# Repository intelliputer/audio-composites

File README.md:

## audio-composites

Since just seeing isn't believing.

## Intellivision mono audio line driver

This repository now contains a standalone audio-output prototype for the NTSC
Intellivision I, Intellivision II, and Sears 497.75022. It taps the console's
pre-RF mono audio, buffers it with a two-transistor gain/line-driver stage,
and returns a buffered mono line to the video-composite board's audio-output
connection.
It does not create stereo or alter the console's sound generation.

The project is intentionally separate from the composite-video board so audio
level, hum, loading, and video interaction can be tested independently. It is
intended to mount as a daughterboard beside that board, using four short wires:
raw audio, buffered audio return, +5 V, and ground. The video board's original
straight-through audio capacitor is bypassed.

### Current status: routed prototype, not yet fabrication-ready

[`project/intv-audio-line-driver.kicad_pcb`](project/intv-audio-line-driver.kicad_pcb)
is a fully routed KiCad Rev. A board. Its routing report has zero DRC
violations and zero unconnected pads. It remains explicitly marked **DO NOT
FAB** because the inherited KiCad schematic has not yet been rewritten to
match the new audio netlist, and the circuit still requires bench validation.

The circuit, component values, and first-article checks are defined in
[`project/REV-A-CIRCUIT.md`](project/REV-A-CIRCUIT.md). The placement can be
recreated through KiCad Flatpak with
[`project/tools/generate_rev_a_pcb.py`](project/tools/generate_rev_a_pcb.py).

The next compact, hand-assembled revision is specified in
[`project/REV-B-KA358-PDIP.md`](project/REV-B-KA358-PDIP.md). It replaces the
discrete stage with a KA358-compatible PDIP-8 dual op amp. Its enlarged
two-layer through-hole routing handoff is in
[`project/intv-audio-line-driver-rev-b.kicad_pcb`](project/intv-audio-line-driver-rev-b.kicad_pcb);
it is deliberately marked **DO NOT FAB** pending a reviewed schematic and
manual routing/DRC cleanup.

Before any fabrication release:

1. Redraw the KiCad schematic from the Rev. A circuit contract.
2. Update the PCB from that schematic and rerun ERC/DRC.
3. Test a first article under a line-level load.

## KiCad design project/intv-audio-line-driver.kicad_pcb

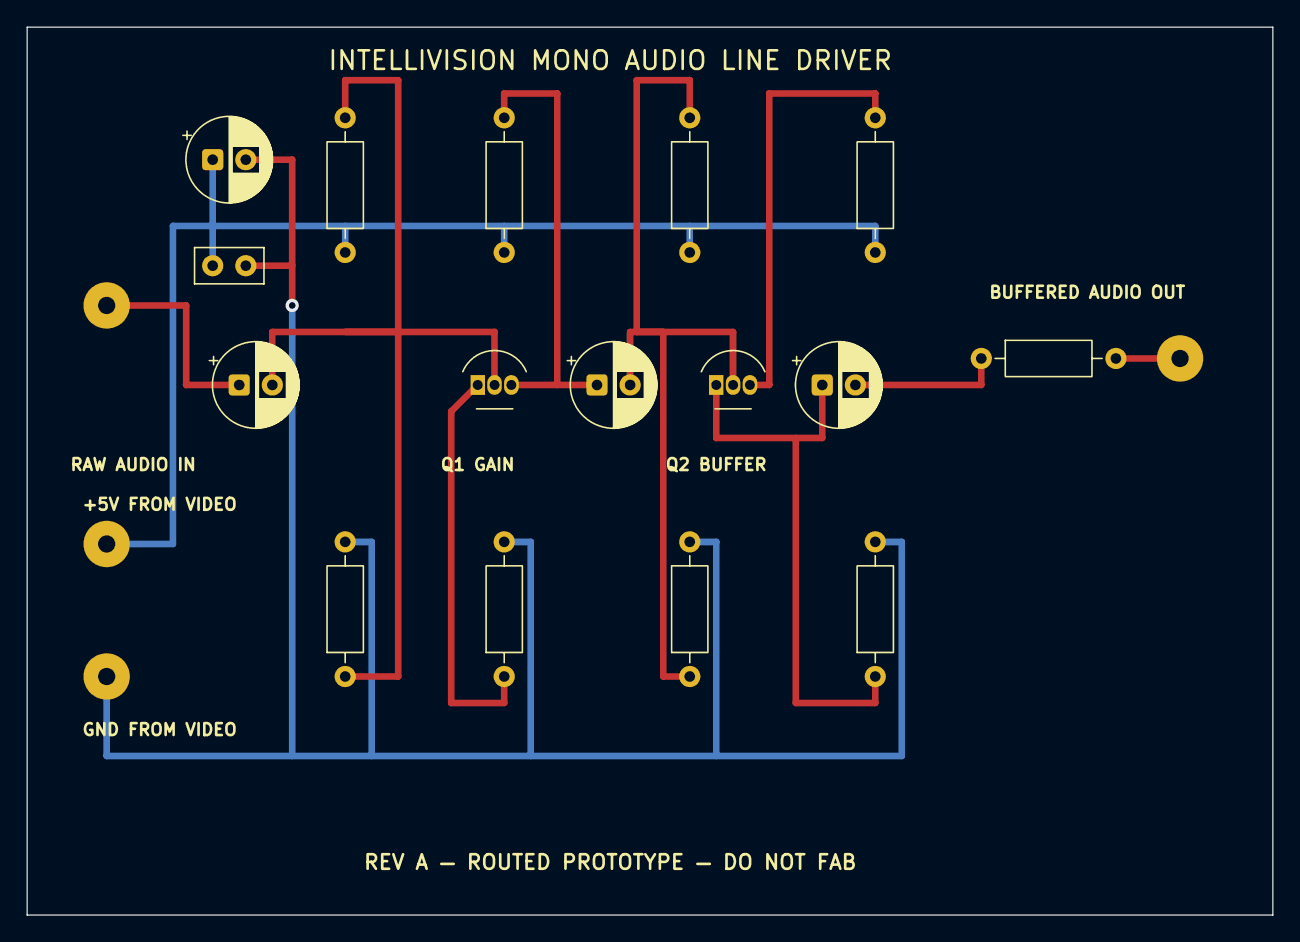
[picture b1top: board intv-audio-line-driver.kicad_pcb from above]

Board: 2 copper layers, 94.0 x 67.0 mm, 20 parts (0 on the bottom side), 11 nets.

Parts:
C1, C2: 10u; CP_Radial_D6.3mm_P2.50mm
C3, C4: 100u; CP_Radial_D6.3mm_P2.50mm
C5: 100n; C_Disc_D5.0mm_W2.5mm_P2.50mm
J1: RAW AUD IN; WirePad_1x01_D3.5mm_Drill1.3mm
J2: BUF AUD OUT; WirePad_1x01_D3.5mm_Drill1.3mm
J3: +5V FROM VID; WirePad_1x01_D3.5mm_Drill1.3mm
J4: GND FROM VID; WirePad_1x01_D3.5mm_Drill1.3mm
Q1, Q2: 2N3904; TO-92_Inline_OAR175
R1: 68k; R_Axial_DIN0207_L6.3mm_D2.5mm_P10.16mm_Horizontal
R2: 22k; R_Axial_DIN0207_L6.3mm_D2.5mm_P10.16mm_Horizontal
R3: 4.7k; R_Axial_DIN0207_L6.3mm_D2.5mm_P10.16mm_Horizontal
R4, R8, R9: 1k; R_Axial_DIN0207_L6.3mm_D2.5mm_P10.16mm_Horizontal
R5, R6: 33k; R_Axial_DIN0207_L6.3mm_D2.5mm_P10.16mm_Horizontal
R7: 0R; R_Axial_DIN0207_L6.3mm_D2.5mm_P10.16mm_Horizontal

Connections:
+5V: C4.1, C5.1, J3.1, R1.1, R3.1, R5.1, R7.1
AUDIO_BUS: C3.2, R9.1
AUD_IN: C1.1, J1.1
AUD_OUT: J2.1, R9.2
GND: C4.2, C5.2, J4.1, R2.2, R4.2, R6.2, R8.2
Q1_BASE: C1.2, Q1.2, R1.2, R2.1
Q1_COL: C2.1, Q1.3, R3.2
Q1_EM: Q1.1, R4.1
Q2_BASE: C2.2, Q2.2, R5.2, R6.1
Q2_COL: Q2.3, R7.2
Q2_EM: C3.1, Q2.1, R8.1

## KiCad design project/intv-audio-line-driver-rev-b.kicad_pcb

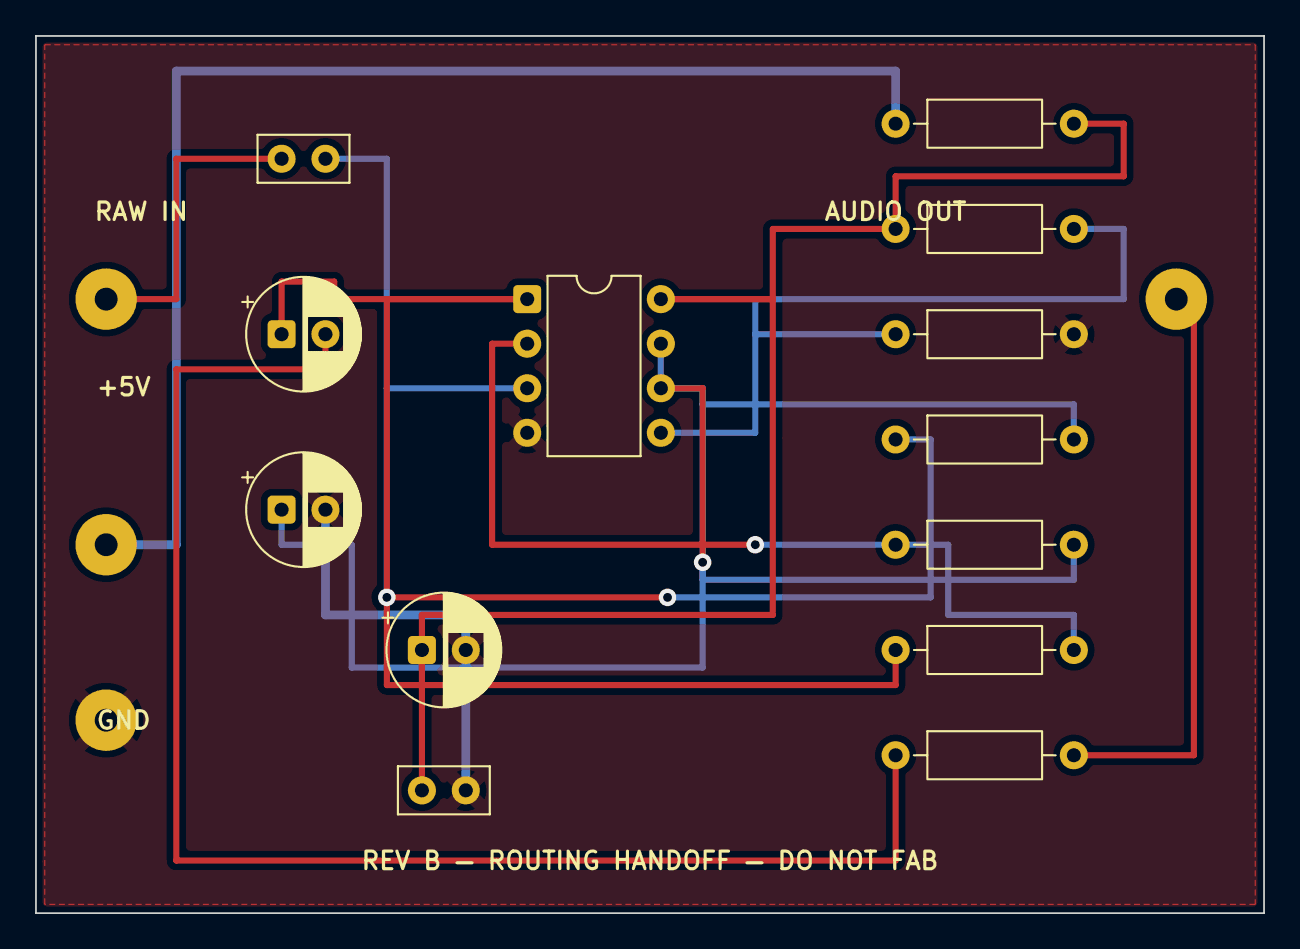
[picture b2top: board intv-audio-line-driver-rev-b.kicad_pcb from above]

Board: 2 copper layers, 70.0 x 50.0 mm, 17 parts (0 on the bottom side), 11 nets.

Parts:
C1: 1u; C_Disc_D5.0mm_W2.5mm_P2.50mm
C2, C3: 47u; CP_Radial_D6.3mm_P2.50mm
C4: 10u; CP_Radial_D6.3mm_P2.50mm
C5: 100n; C_Disc_D5.0mm_W2.5mm_P2.50mm
J1: RAW AUDIO IN; WirePad_1x01_D3.5mm_Drill1.3mm
J2: BUFFERED AUDIO OUT; WirePad_1x01_D3.5mm_Drill1.3mm
J3: +5V FROM VIDEO; WirePad_1x01_D3.5mm_Drill1.3mm
J4: GND FROM VIDEO; WirePad_1x01_D3.5mm_Drill1.3mm
R1: 10R; R_Axial_DIN0207_L6.3mm_D2.5mm_P10.16mm_Horizontal
R2, R3, R5, R6: 10k; R_Axial_DIN0207_L6.3mm_D2.5mm_P10.16mm_Horizontal
R4: 100k; R_Axial_DIN0207_L6.3mm_D2.5mm_P10.16mm_Horizontal
R7: 1k; R_Axial_DIN0207_L6.3mm_D2.5mm_P10.16mm_Horizontal
U1: KA358; DIP-8_W7.62mm

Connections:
+5V: J3.1, R1.1
AUDIO_BUS: C2.2, R7.1
AV5: C4.1, C5.1, R1.2, R2.1, U1.8
BUFFERED_AUD_OUT: J2.1, R7.2
GND: C3.2, C4.2, C5.2, J4.1, R3.2, U1.4
IN_BIASED: C1.2, R4.1, U1.3
RAW_AUD_IN: C1.1, J1.1
U1A_MINUS: R5.1, R6.2, U1.2
U1A_OUT: C2.1, R6.1, U1.1
VREF: C3.1, R4.2, R5.2, U1.6, U1.7
VREF_RAW: R2.2, R3.1, U1.5
